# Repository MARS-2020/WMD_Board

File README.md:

# WMD_Board
Main PCB for the wrist mounted device

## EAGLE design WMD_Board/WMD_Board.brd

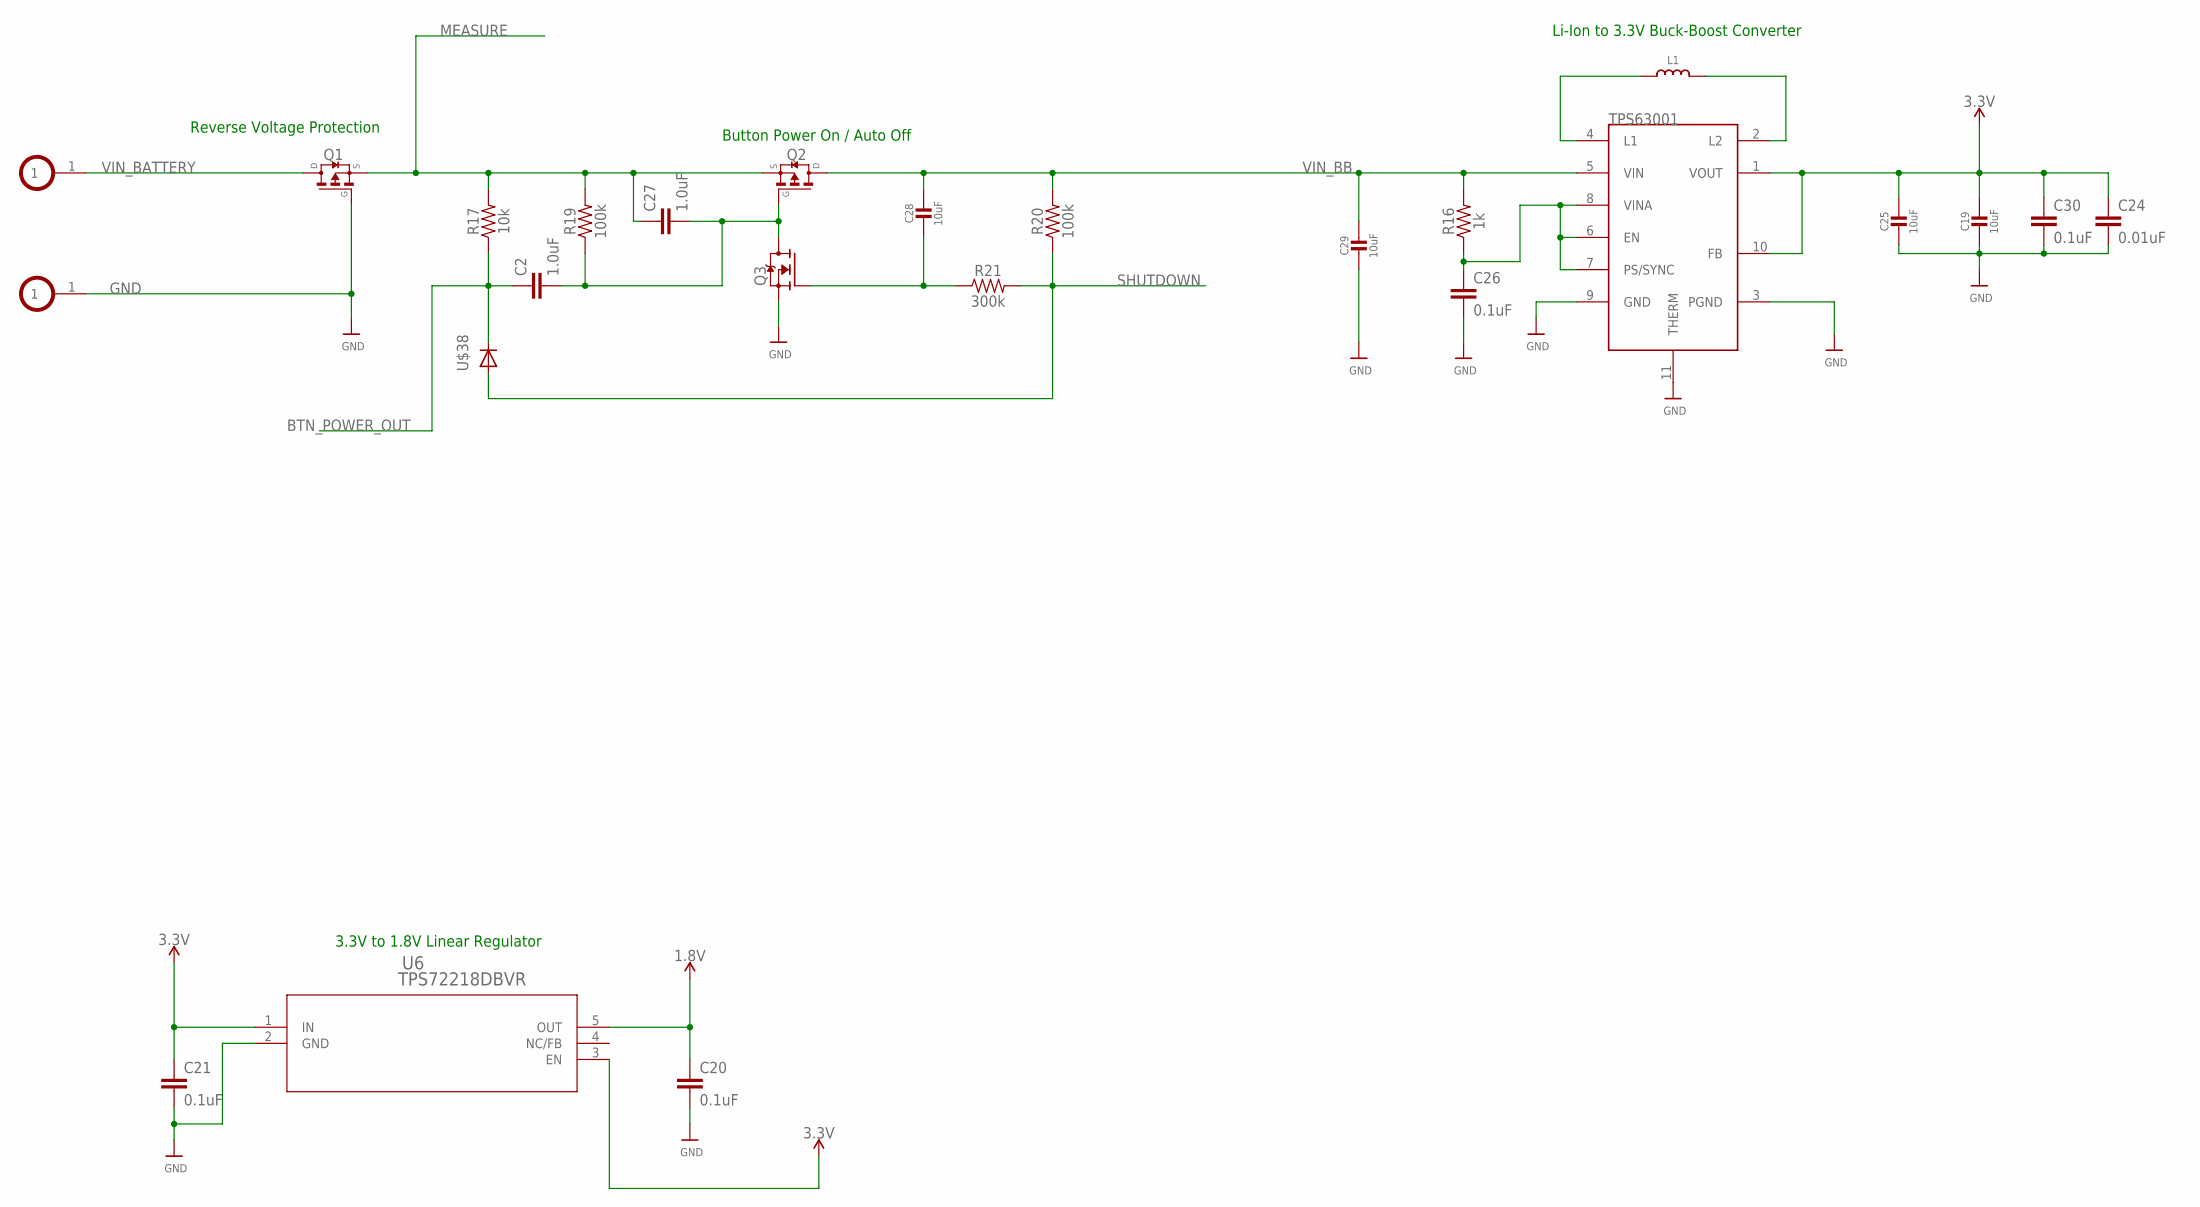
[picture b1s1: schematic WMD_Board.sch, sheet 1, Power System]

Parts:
C2, C27: 1.0uF; 0603
C19, C25, C28, C29: 10uF; 0805-NO
C20, C21, C26, C30: 0.1uF; 0603
C24: 0.01uF; 0603
L1: 2.2uH/NRH2412T2R2MNGH; INDUCTOR_TAIYOYUDEN_NRH2412T
Q1, Q2: SI2323DS-T1-E3; SOT23
Q3: SI2312BDS; SOT23
R16: 1k; 0603
R17: 10k; 0603
R19, R20: 100k; 0603
R21: 300k; 0603
U6: TPS72218DBVR; DBV5
U$22: TPS63001
U$38: TS4148C_RZG; C0805K
U$40, U$41: BATTERY_HOLE

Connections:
1.8V: C20.1, U6.5 (OUT); also elsewhere on the board
3.3V: C19.1, C21.1, C24.1, C25.1, C30.1, U6.1 (IN), U6.3 (EN), U$22.1 (VOUT), U$22.10 (FB); also elsewhere on the board
BTN_POWER_OUT: C2.1, R17.1, U$38.C; also elsewhere on the board
GND: C19.2, C20.2, C21.2, C24.2, C25.2, C26.2, C29.2, C30.2, Q1.1 (G), Q3.2 (S), U6.2 (GND), U$22.3 (PGND), U$22.9 (GND), U$22.11 (THERM), U$41.1; also elsewhere on the board
MEASURE: C27.1, Q1.2 (S), Q2.2 (S), R17.2, R19.2; also elsewhere on the board
unnamed: L1.1, U$22.4 (L1)
unnamed: L1.2, U$22.2 (L2)
unnamed: C26.1, R16.1, U$22.6 (EN), U$22.7 (PS/SYNC), U$22.8 (VINA)
unnamed: C28.2, Q3.1 (G), R21.1
unnamed: C2.2, C27.2, Q2.1 (G), Q3.3 (D), R19.1
SHUTDOWN: R20.1, R21.2, U$38.A; also elsewhere on the board
VIN_BATTERY: Q1.3 (D), U$40.1
VIN_BB: C28.1, C29.1, Q2.3 (D), R16.2, R20.2, U$22.5 (VIN)

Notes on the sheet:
3.3V to 1.8V Linear Regulator
Li-Ion to 3.3V Buck-Boost Converter
Reverse Voltage Protection
Button Power On / Auto Off

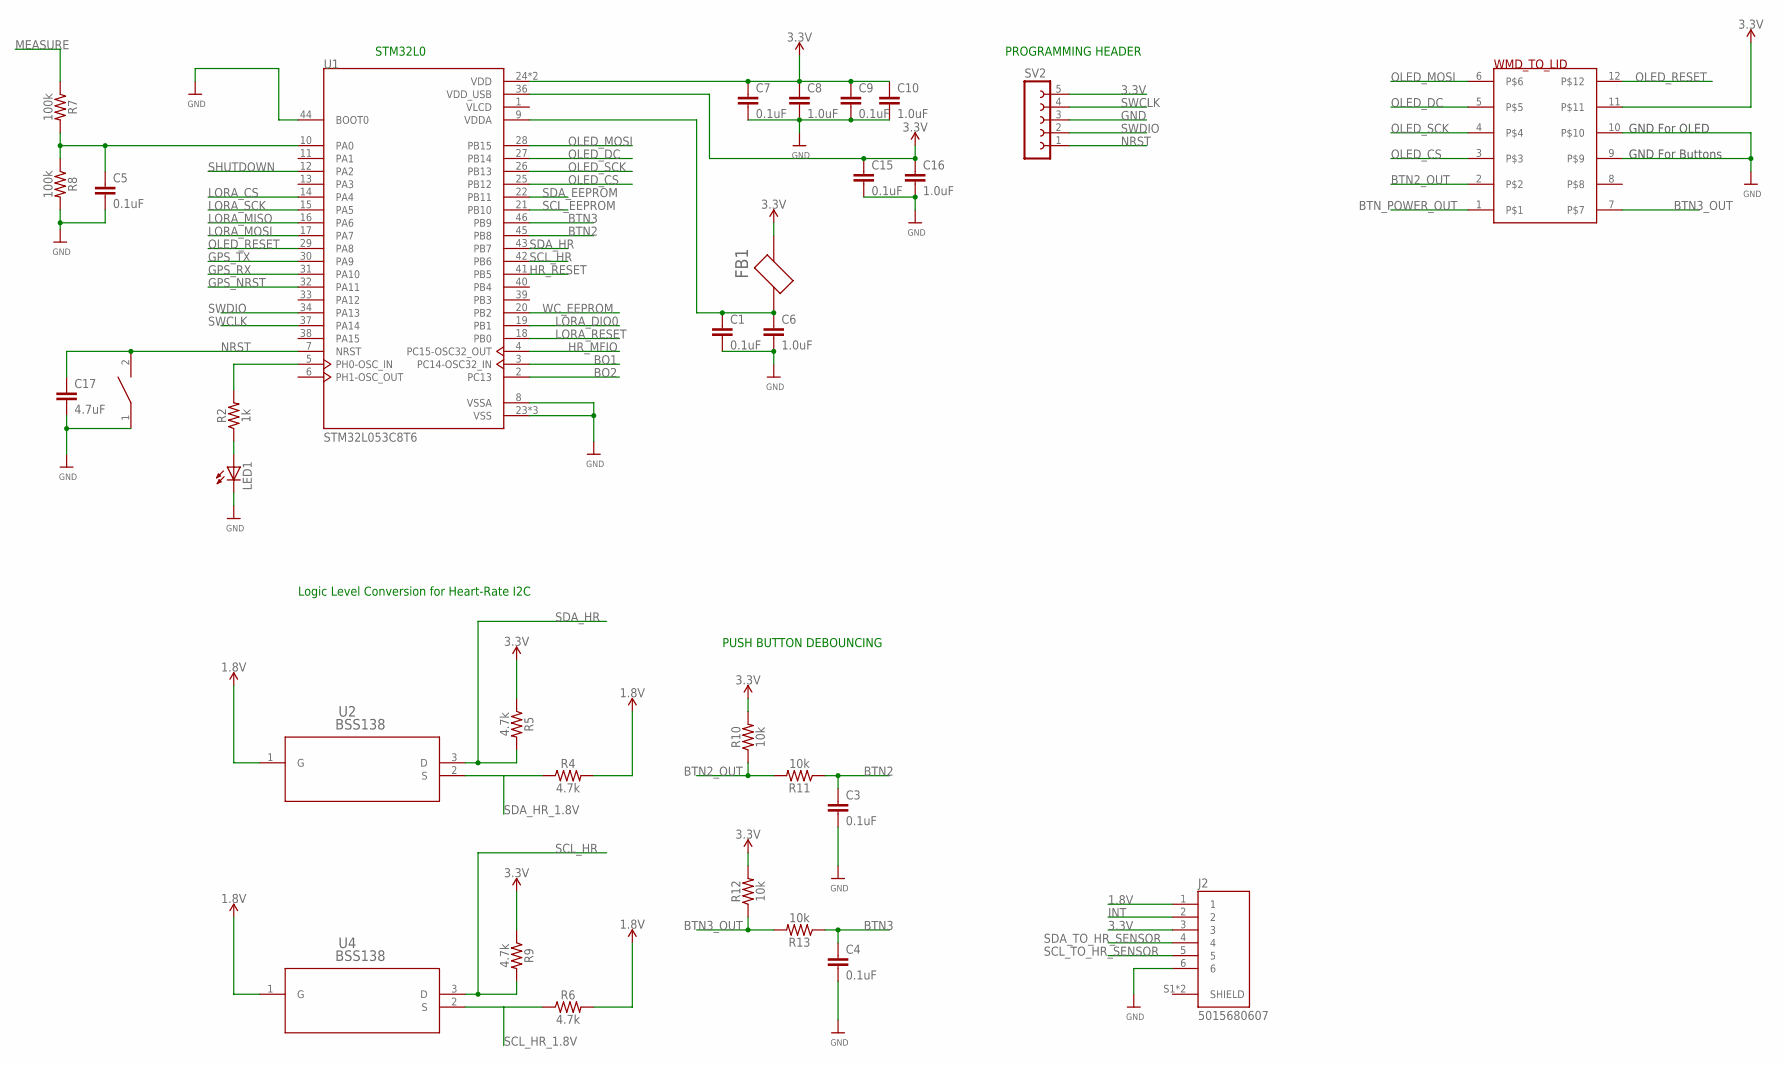
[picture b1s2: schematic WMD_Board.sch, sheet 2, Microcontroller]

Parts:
C1, C3, C4, C5, C7, C9, C15: 0.1uF; 0603
C6, C8, C10, C16: 1.0uF; 0603
C17: 4.7uF; 0603
FB1: FERRITE_BEAD; BEADC1608X100N
J2: 5015680607; MOLEX_5015680607
LED1: LEDCHIP-LED0805; CHIP-LED0805
R2: 1k; 0603
R4, R5, R6, R9: 4.7k; 0603
R7, R8: 100k; 0603
R10, R11, R12, R13: 10k; 0603
RESET: SWITCH; SW_2512
SV2: FE05-1
U1: STM32L053C8T6; QFP50P900X900X160-48N
U2, U4: BSS138; SOT-23-3L
U$20: TS_DR_6; TST_DR_6

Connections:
1.8V: J2.1, R4.2, R6.2, U2.1 (G), U4.1 (G); also elsewhere on the board
3.3V: C7.1, C8.1, C9.1, C10.1, C15.1, C16.1, FB1.1, J2.3, R5.1, R9.1, R10.2, R12.2, SV2.5, U1.24 (VDD), U1.36 (VDD_USB), U1.48 (VDD), U$20.11; also elsewhere on the board
BO1: U1.3 (PC14-OSC32_IN)
BO2: U1.2 (PC13)
BTN2: C3.1, R11.1, U1.45 (PB8)
BTN2_OUT: R10.1, R11.2, U$20.2
BTN3: C4.1, R13.1, U1.46 (PB9)
BTN3_OUT: R12.1, R13.2, U$20.7
BTN_POWER_OUT: U$20.1; also elsewhere on the board
GND: C1.2, C3.2, C4.2, C5.2, C6.2, C7.2, C8.2, C9.2, C10.2, C15.2, C16.2, C17.2, J2.6, LED1.C, R8.2, RESET.1, SV2.3, U1.8 (VSSA), U1.23 (VSS), U1.35 (VSS), U1.44 (BOOT0), U1.47 (VSS), U$20.9, U$20.10; also elsewhere on the board
GPS_NRST: U1.32 (PA11); also elsewhere on the board
GPS_RX: U1.31 (PA10); also elsewhere on the board
GPS_TX: U1.30 (PA9); also elsewhere on the board
HR_MFIO: U1.4 (PC15-OSC32_OUT); also elsewhere on the board
HR_RESET: U1.41 (PB5); also elsewhere on the board
INT: J2.2; also elsewhere on the board
LORA_CS: U1.14 (PA4); also elsewhere on the board
LORA_DIO0: U1.19 (PB1); also elsewhere on the board
LORA_MISO: U1.16 (PA6); also elsewhere on the board
LORA_MOSI: U1.17 (PA7); also elsewhere on the board
LORA_RESET: U1.18 (PB0); also elsewhere on the board
LORA_SCK: U1.15 (PA5); also elsewhere on the board
MEASURE: R7.1; also elsewhere on the board
unnamed: LED1.A, R2.1
unnamed: C5.1, R7.2, R8.1, U1.10 (PA0)
unnamed: C1.1, C6.1, FB1.2, U1.9 (VDDA)
unnamed: R2.2, U1.5 (PH0-OSC_IN)
NRST: C17.1, RESET.2, SV2.1, U1.7 (NRST)
OLED_CS: U1.25 (PB12), U$20.3
OLED_DC: U1.27 (PB14), U$20.5
OLED_MOSI: U1.28 (PB15), U$20.6
OLED_RESET: U1.29 (PA8), U$20.12
OLED_SCK: U1.26 (PB13), U$20.4
SCL_EEPROM: U1.21 (PB10); also elsewhere on the board
SCL_HR: R9.2, U1.42 (PB6), U4.3 (D)
SCL_HR_1.8V: R6.1, U4.2 (S); also elsewhere on the board
SCL_TO_HR_SENSOR: J2.5; also elsewhere on the board
SDA_EEPROM: U1.22 (PB11); also elsewhere on the board
SDA_HR: R5.2, U1.43 (PB7), U2.3 (D)
SDA_HR_1.8V: R4.1, U2.2 (S); also elsewhere on the board
SDA_TO_HR_SENSOR: J2.4; also elsewhere on the board
SHUTDOWN: U1.12 (PA2); also elsewhere on the board
SWCLK: SV2.4, U1.37 (PA14)
SWDIO: SV2.2, U1.34 (PA13)
WC_EEPROM: U1.20 (PB2); also elsewhere on the board

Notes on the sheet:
PROGRAMMING HEADER
STM32L0
Logic Level Conversion for Heart-Rate I2C
PUSH BUTTON DEBOUNCING
GND For Buttons
GND For OLED

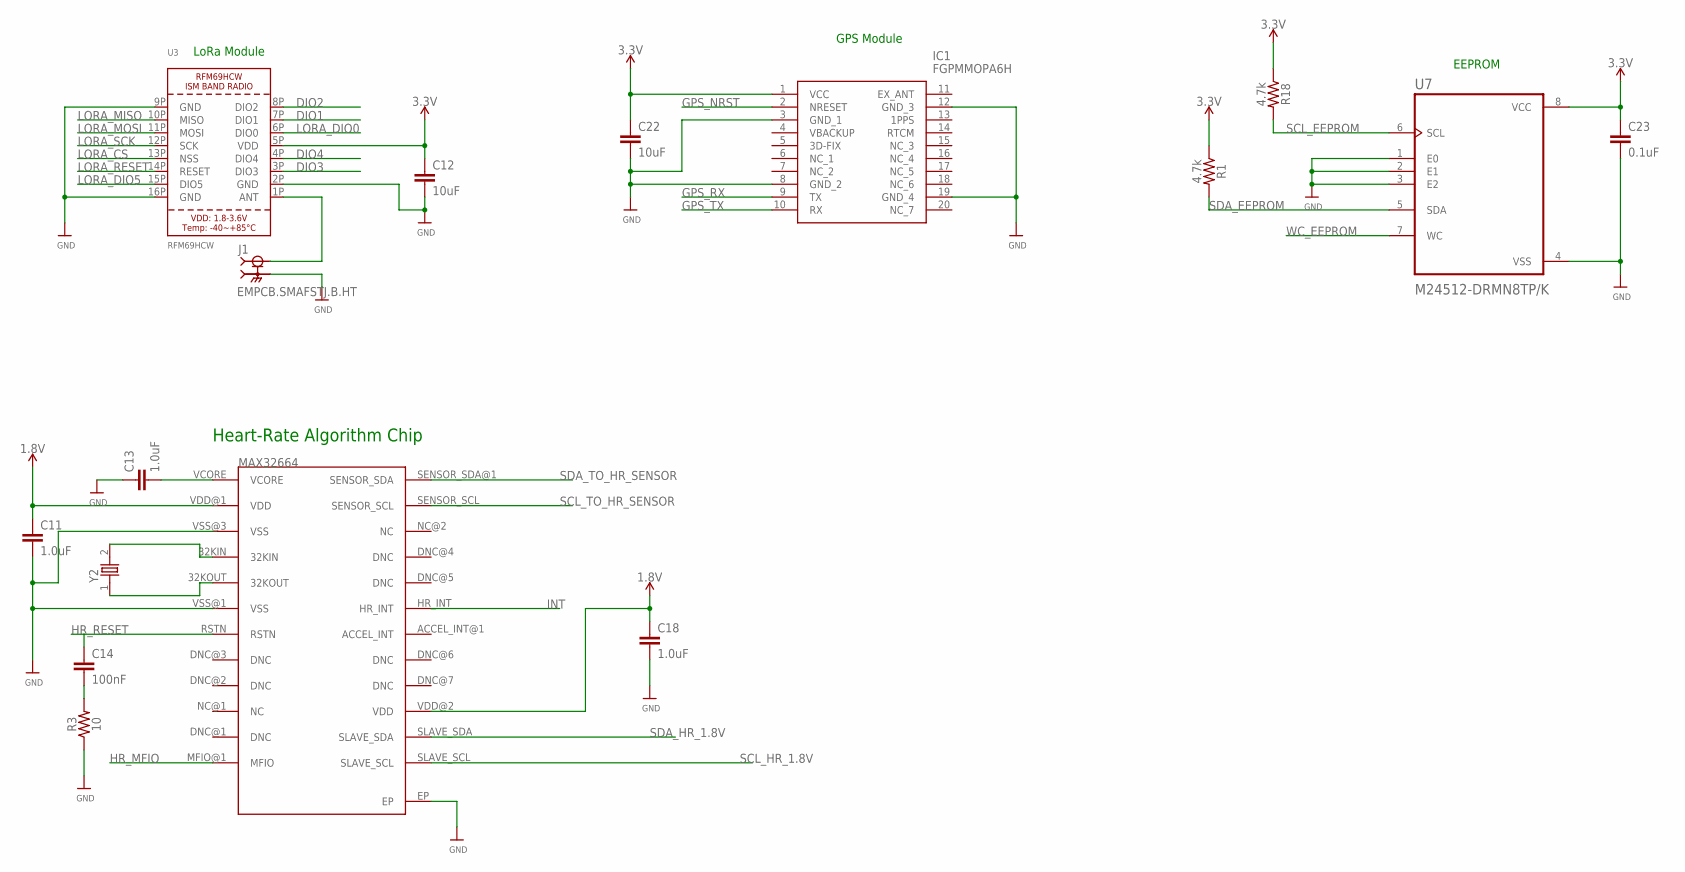
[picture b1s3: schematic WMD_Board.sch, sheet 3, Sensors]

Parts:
C11, C13, C18: 1.0uF; 0603
C12, C22: 10uF; 0603
C14: 100nF; 0603
C23: 0.1uF; 0603
IC1: FGPMMOPA6H
J1: EMPCB.SMAFSTJ.B.HT; TAOGLAS_EMPCB.SMAFSTJ.B.HT
R1, R18: 4.7k; 0603
R3: 10; 0603
U3: RFM69HCW; RFMHCW_SMT
U7: M24512-DRMN8TP/K; SOIC127P600X175-8N
U$10: MAX32664_TQFN; MAX32664
Y2: ABS06-107-32.768KHZ-T; XTAL_ABS06-107-32.768KHZ-T

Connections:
1.8V: C11.1, C18.1, U$10.VDD@1 (VDD), U$10.VDD@2 (VDD); also elsewhere on the board
3.3V: C12.1, C22.1, C23.1, IC1.1 (VCC), R1.1, R18.1, U3.5P (VDD), U7.8 (VCC); also elsewhere on the board
DIO1: U3.7P (DIO1)
DIO2: U3.8P (DIO2)
DIO3: U3.3P (DIO3)
DIO4: U3.4P (DIO4)
GND: C11.2, C12.2, C13.1, C18.2, C22.2, C23.2, IC1.3 (GND_1), IC1.8 (GND_2), IC1.12 (GND_3), IC1.19 (GND_4), J1.SH1 (2), J1.SH2 (2), J1.SH3 (2), J1.SH4 (2), R3.1, U3.2P (GND), U3.9P (GND), U3.16P (GND), U7.1 (E0), U7.2 (E1), U7.3 (E2), U7.4 (VSS), U$10.EP, U$10.VSS@1 (VSS), U$10.VSS@3 (VSS); also elsewhere on the board
GPS_NRST: IC1.2 (NRESET); also elsewhere on the board
GPS_RX: IC1.9 (TX); also elsewhere on the board
GPS_TX: IC1.10 (RX); also elsewhere on the board
HR_MFIO: U$10.MFIO@1 (MFIO); also elsewhere on the board
HR_RESET: C14.1, U$10.RSTN; also elsewhere on the board
INT: U$10.HR_INT; also elsewhere on the board
LORA_CS: U3.13P (NSS); also elsewhere on the board
LORA_DIO0: U3.6P (DIO0); also elsewhere on the board
LORA_DIO5: U3.15P (DIO5)
LORA_MISO: U3.10P (MISO); also elsewhere on the board
LORA_MOSI: U3.11P (MOSI); also elsewhere on the board
LORA_RESET: U3.14P (RESET); also elsewhere on the board
LORA_SCK: U3.12P (SCK); also elsewhere on the board
unnamed: C13.2, U$10.VCORE
unnamed: J1.1, U3.1P (ANT)
unnamed: C14.2, R3.2
unnamed: U$10.32KIN, Y2.2
unnamed: U$10.32KOUT, Y2.1
SCL_EEPROM: R18.2, U7.6 (SCL); also elsewhere on the board
SCL_HR_1.8V: U$10.SLAVE_SCL; also elsewhere on the board
SCL_TO_HR_SENSOR: U$10.SENSOR_SCL; also elsewhere on the board
SDA_EEPROM: R1.2, U7.5 (SDA); also elsewhere on the board
SDA_HR_1.8V: U$10.SLAVE_SDA; also elsewhere on the board
SDA_TO_HR_SENSOR: U$10.SENSOR_SDA@1 (SENSOR_SDA); also elsewhere on the board
WC_EEPROM: U7.7 (WC); also elsewhere on the board

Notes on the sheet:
LoRa Module
Heart-Rate Algorithm Chip
GPS Module
EEPROM

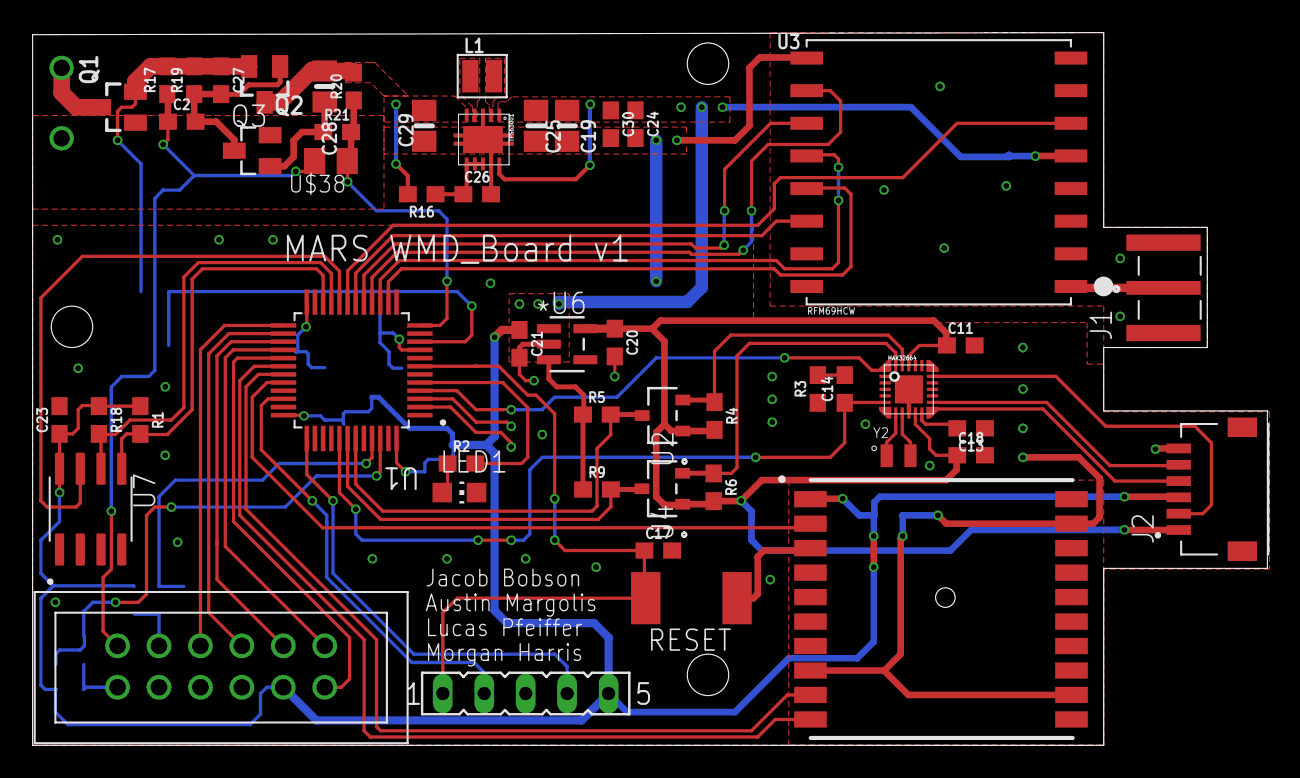
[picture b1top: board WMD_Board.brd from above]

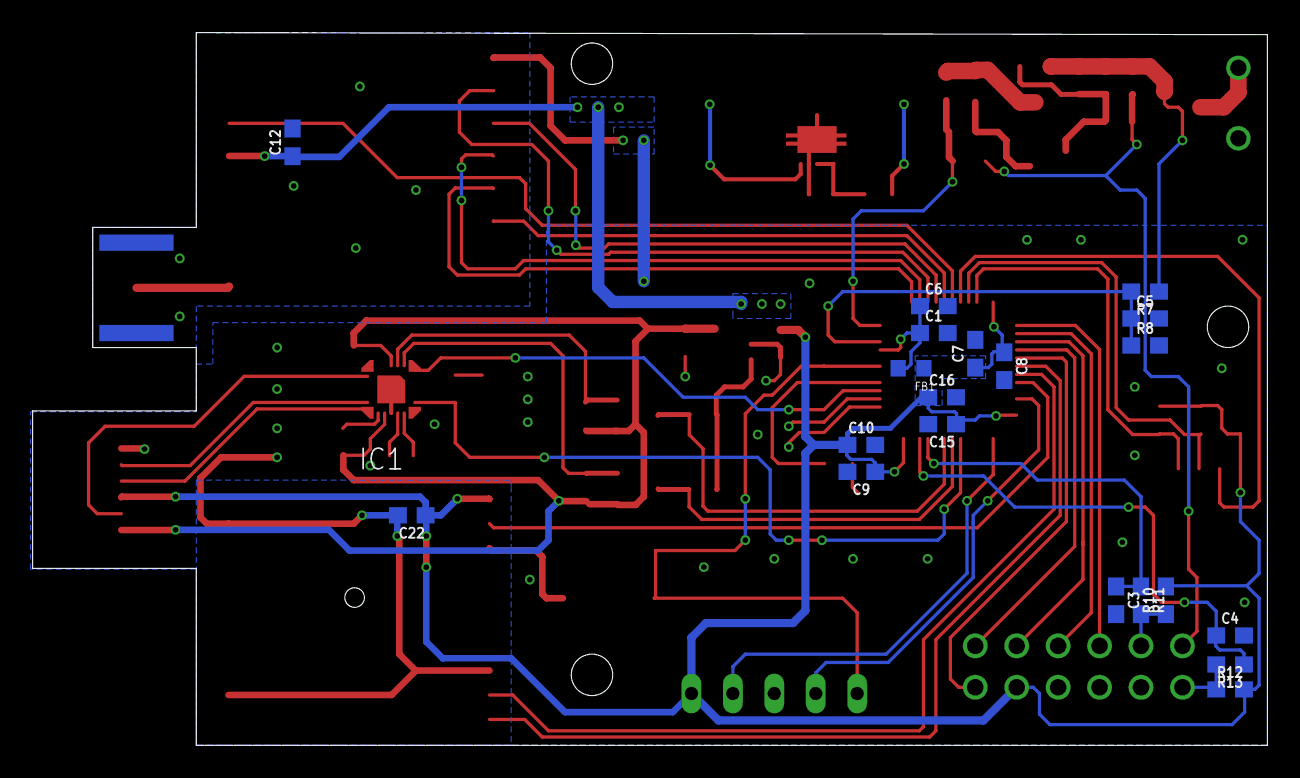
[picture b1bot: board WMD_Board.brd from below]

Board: 2 copper layers, 75.7 x 43.7 mm, 73 parts (20 on the bottom side), 55 nets.

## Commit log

2020-02-12 Start
2020-02-13 Added algorithm chip
2020-02-18 Schematic Progress
2020-02-18 Schematic
2020-02-18 More Schematic Work
2020-02-19 Added Level Shifters
2020-02-19 Schematic work
2020-02-26 stuff
2020-02-26 added gps module
2020-02-28 Added lots of schematic stuff
2020-02-29 Board routing started
2020-03-01 lots of routing stuff
2020-03-01 noise snubber
2020-03-02 Routed
2020-03-02 Magical Changes that I'm not sure are real *thinking emoticon*
2020-03-02 Ground Vias and Silkscreen
2020-03-02 Routed MFIO Pin (routing completed)
2020-03-02 hole spacing
2020-03-04 added heartbeat led, ferrite bead, pin breakout
2020-03-11 made changes besides zener diode
2020-03-13 Final Modifications

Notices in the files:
parts and their libraries:
SparkFun-Capacitors: Licensing: Creative Commons ShareAlike 4.0 International - https://creativecommons.org/licenses/by-sa/4.0
microbuilder: This work is placed in the public domain, and may be freely used for commercial and non-commercial work with the following conditions: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
